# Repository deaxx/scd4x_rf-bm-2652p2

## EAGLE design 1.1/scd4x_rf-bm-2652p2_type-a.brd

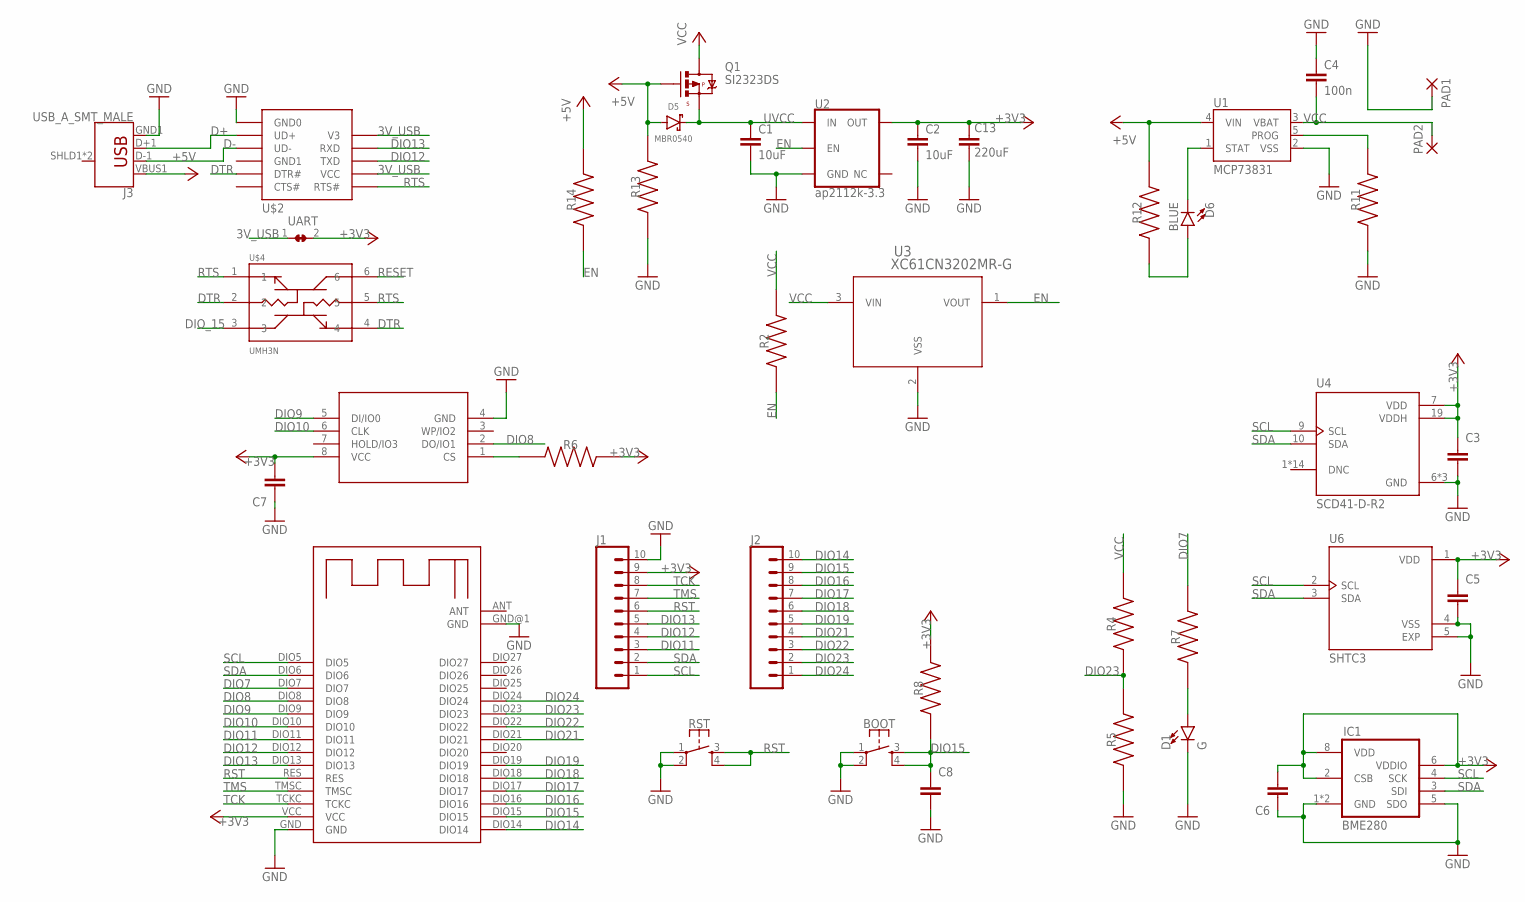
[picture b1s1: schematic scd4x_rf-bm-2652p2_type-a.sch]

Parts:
BOOT: MOMENTARY-SWITCH-SPST-2-SMD-4.6X2.8MM; TACTILE_SWITCH_SMD_4.6X2.8MM
C1, C2: 10uF; 0603
C3, C5, C6, C8: 100nF; CAPC1005X40N
C4: 100n; 0603
C7: 100n; CAPC1005X40N
C13: 220uF; CAPM7343X310
D1: G; LED-0603
D5: MBR0540; SOD-323
D6: BLUE; LED-0603
IC1: BME280
J1, J2: CONN_10NO_SILK_PTH_FEMALE; 1X10_NO_SILK
J3: USB_A_SMT_MALE; USB-A-SMT-MALE
PAD1, PAD2: WIREPADSMD1,27-254; SMD1,27-2,54
Q1: SI2323DS; SOT23
R2, R14: 10k; RESC1005X40N
R4, R5: 382k; RESC1005X40N
R6, R7, R12: 2.2k; RESC1005X40N
R8: 5.1M; RESC1005X40N
R11: 2k; RESC1005X40N
R13: 100k; RESC1005X40N
RST: MOMENTARY-SWITCH-SPST-2-SMD-4.6X2.8MM; TACTILE_SWITCH_SMD_4.6X2.8MM
U1: MCP73831; SOT23-5
U2: ap2112k-3.3; SOT23-5
U3: XC61CN3202MR-G; XC61C_SOT-23_TOR
U4: SCD41-D-R2; XDCR_SCD41-D-R2
U6: SHTC3; SON100P200X200X80-5N
U$1: RF-BM-2652P2
U$2: CH340K; ESSOP10
U$3: MX25R8035FM1IL0; SO-8
U$4: UMH3N; SOP65P210X100-6N
UART: UART; SMALL_SOLDER_JUMPER_CLOSED

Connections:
3V_USB: U$2.P$6 (VCC), U$2.P$9 (V3), UART.1
+3V3: C2.1, C3.1, C5.1, C6.2, C7.2, C13.1, IC1.2 (CSB), IC1.6 (VDDIO), IC1.8 (VDD), J1.9, R6.2, R8.2, U2.5 (OUT), U4.7 (VDD), U4.19 (VDDH), U6.1 (VDD), U$1.VCC, U$3.8 (VCC), UART.2
+5V: D5.A, J3.VBUS1 (VBUS), Q1.1 (G), R12.2, R13.2, R14.2, U1.4 (VIN)
D+: J3.D+1 (D+), U$2.P$0 (UD+)
D-: J3.D-1 (D-), U$2.P$1 (UD-)
DIO7: R7.2, U$1.DIO7
DIO8: U$1.DIO8, U$3.2 (DO/IO1)
DIO9: U$1.DIO9, U$3.5 (DI/IO0)
DIO10: U$1.DIO10, U$3.6 (CLK)
DIO11: J1.3, U$1.DIO11
DIO12: J1.4, U$1.DIO12, U$2.P$7 (TXD)
DIO13: J1.5, U$1.DIO13, U$2.P$8 (RXD)
DIO14: J2.10, U$1.DIO14
DIO15: BOOT.3, BOOT.4, C8.1, J2.9, R8.1, U$1.DIO15
DIO16: J2.8, U$1.DIO16
DIO17: J2.7, U$1.DIO17
DIO18: J2.6, U$1.DIO18
DIO19: J2.5, U$1.DIO19
DIO21: J2.4, U$1.DIO21
DIO22: J2.3, U$1.DIO22
DIO23: J2.2, R4.1, R5.2, U$1.DIO23
DIO24: J2.1, U$1.DIO24
DIO_15: U$4.3
DTR: U$2.P$3 (DTR#), U$4.2, U$4.4
EN: R2.1, R14.1, U2.3 (EN), U3.1 (VOUT)
GND: BOOT.1, BOOT.2, C1.2, C2.2, C3.2, C4.1, C5.2, C6.1, C7.1, C8.2, C13.2, D1.C, IC1.1 (GND), IC1.5 (SDO), IC1.7 (GND), J1.10, J3.GND1 (GND), PAD1.1, R5.1, R11.1, R13.1, RST.1, RST.2, U1.2 (VSS), U2.2 (GND), U3.2 (VSS), U4.6 (GND), U4.20 (GND), U4.21 (GND), U6.4 (VSS), U6.5 (EXP), U$1.GND, U$1.GND@1 (GND), U$2.P$10 (GND0), U$3.4 (GND)
unnamed: D1.A, R7.1
unnamed: R6.1, U$3.1 (CS)
unnamed: R11.2, U1.5 (PROG)
unnamed: D6.A, R12.1
unnamed: D6.C, U1.1 (STAT)
RESET: U$4.6
RST: J1.6, RST.3, RST.4, U$1.RES
RTS: U$2.P$5 (RTS#), U$4.1, U$4.5
SCL: IC1.4 (SCK), J1.1, U4.9 (SCL), U6.2 (SCL), U$1.DIO5
SDA: IC1.3 (SDI), J1.2, U4.10 (SDA), U6.3 (SDA), U$1.DIO6
TCK: J1.8, U$1.TCKC
TMS: J1.7, U$1.TMSC
UVCC: C1.1, D5.C, Q1.2 (S), U2.1 (IN)
VCC: C4.2, PAD2.1, Q1.3 (D), R2.2, R4.2, U1.3 (VBAT), U3.3 (VIN)

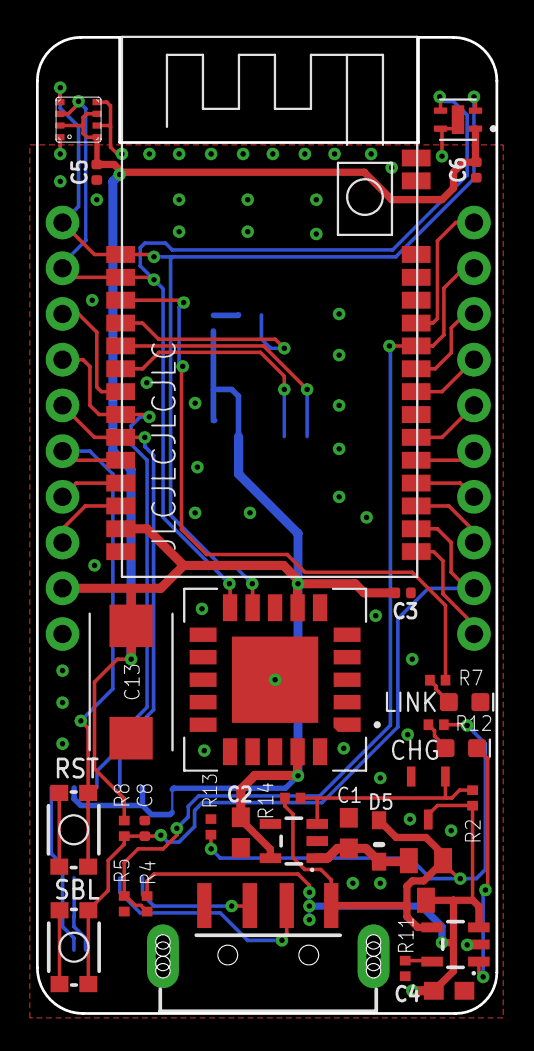
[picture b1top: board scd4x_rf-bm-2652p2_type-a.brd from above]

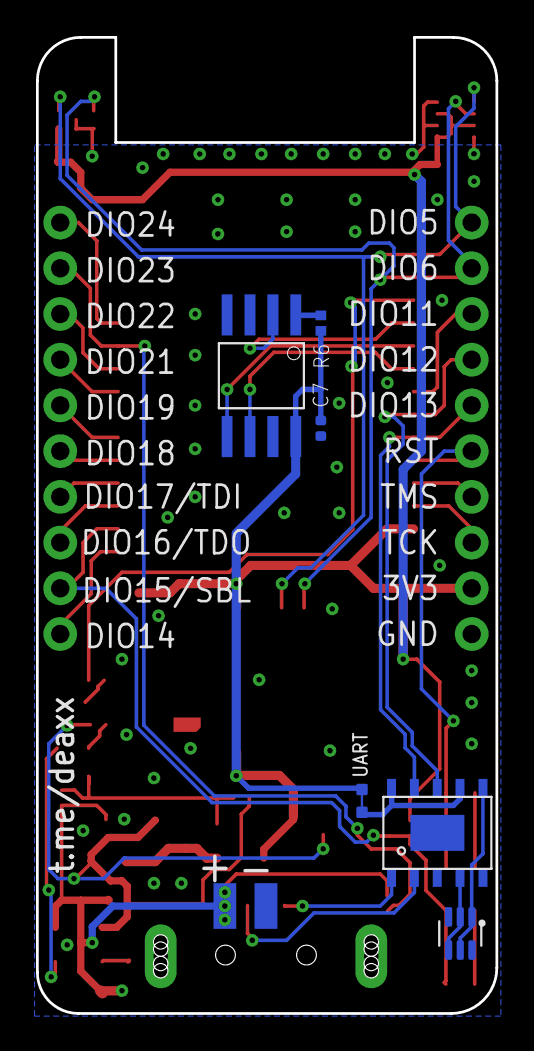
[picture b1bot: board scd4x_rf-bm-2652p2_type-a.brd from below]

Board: 2 copper layers, 25.5 x 54.2 mm, 41 parts (8 on the bottom side), 38 nets.

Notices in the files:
parts and their libraries:
SparkFun-IC-Power: Licensing: Creative Commons ShareAlike 4.0 International - https://creativecommons.org/licenses/by-sa/4.0
